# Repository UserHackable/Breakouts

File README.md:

## Breakouts

A bunch of random breakout boards
## 4ButtonBreakout 

### Board dimensions

* (165000, 125000) original units
* (1.6500, 1.2500) inches
* (41.9100, 31.7500) mm

[gerbers](4ButtonBreakout_gerber.zip?raw=true)

| Front | Back |
| --- | --- |
|  |  |

## 5MMHexaStellaBreakout 

### Board dimensions

* (100000, 100000) original units
* (1.0000, 1.0000) inches
* (25.4000, 25.4000) mm

[gerbers](5MMHexaStellaBreakout_gerber.zip?raw=true)

| Front | Back |
| --- | --- |
|  |  |

## Joystick 

### Board dimensions

* (110000, 125000) original units
* (1.1000, 1.2500) inches
* (27.9400, 31.7500) mm

[gerbers](Joystick_gerber.zip?raw=true)

| Front | Back |
| --- | --- |
|  |  |

## Led_Bar 

### Board dimensions

* (150000, 45000) original units
* (1.5000, 0.4500) inches
* (38.1000, 11.4300) mm

[gerbers](Led_Bar_gerber.zip?raw=true)

| Front | Back |
| --- | --- |
|  |  |

## MinimalDigitalAmp 

### Board dimensions

* (100000, 69994) original units
* (1.0000, 0.6999) inches
* (25.4000, 17.7785) mm

[gerbers](MinimalDigitalAmp_gerber.zip?raw=true)

| Front | Back |
| --- | --- |
|  |  |

## SingleToggleBreakout 

### Board dimensions

* (60000, 64993) original units
* (0.6000, 0.6499) inches
* (15.2400, 16.5082) mm

[gerbers](SingleToggleBreakout_gerber.zip?raw=true)

| Front | Back |
| --- | --- |
|  |  |

## UsbA 

### Board dimensions

* (99951, 47461) original units
* (0.9995, 0.4746) inches
* (25.3876, 12.0551) mm

[gerbers](UsbA_gerber.zip?raw=true)

| Front | Back |
| --- | --- |
|  |  |

## USBMiniBPower 

### Board dimensions

* (70000, 50000) original units
* (0.7000, 0.5000) inches
* (17.7800, 12.7000) mm

[gerbers](USBMiniBPower_gerber.zip?raw=true)

| Front | Back |
| --- | --- |
|  |  |

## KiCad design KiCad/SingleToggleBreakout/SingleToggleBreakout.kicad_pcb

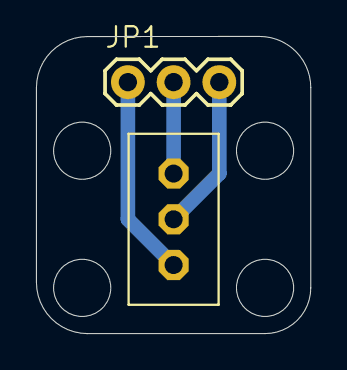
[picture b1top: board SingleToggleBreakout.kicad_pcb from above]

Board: 2 copper layers, 15.2 x 16.5 mm, 6 parts (0 on the bottom side), 3 nets.

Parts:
JP1: 1X03
U$1: SPDTSPDT; TOGGLE_SPDT
UNK_HOLE_0: dummyfp0
UNK_HOLE_1: dummyfp1
UNK_HOLE_2: dummyfp2
UNK_HOLE_3: dummyfp3

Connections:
5V: JP1.2, U$1.3
GND: JP1.1, U$1.1
unnamed: JP1.3, U$1.2

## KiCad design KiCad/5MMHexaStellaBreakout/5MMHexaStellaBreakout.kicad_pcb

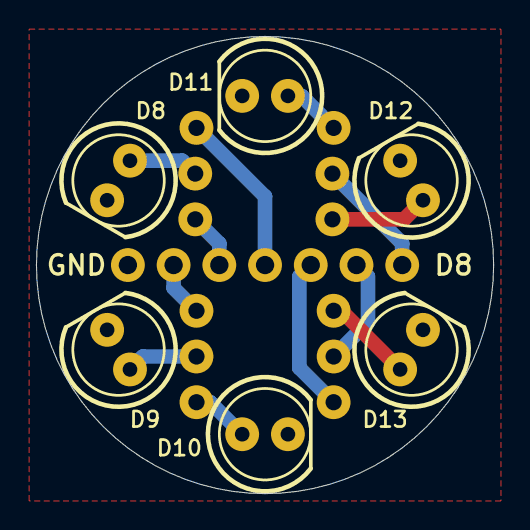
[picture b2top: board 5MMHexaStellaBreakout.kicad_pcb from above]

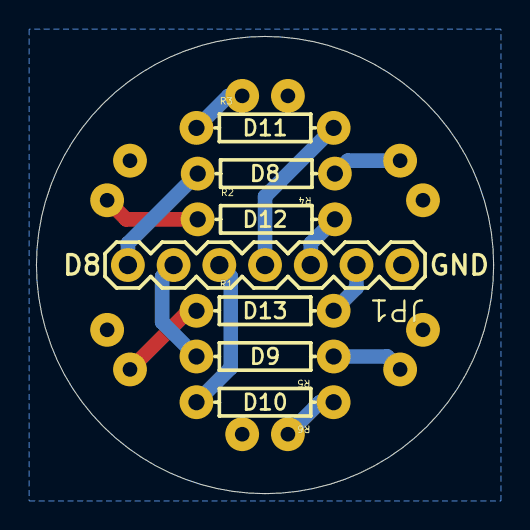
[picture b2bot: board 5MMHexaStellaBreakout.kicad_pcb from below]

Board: 2 copper layers, 25.4 x 25.4 mm, 13 parts (7 on the bottom side), 13 nets.

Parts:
JP1: 1X07
LED1, LED2, LED3, LED4, LED5, LED6: LED5MM
R1, R2, R3, R4, R5, R6: AXIAL-0.3

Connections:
D8: JP1.7, R4.P$2
D9: JP1.6, R5.P$2
D10: JP1.5, R6.P$2
D11: JP1.4, R3.P$2
D12: JP1.3, R2.P$2
D13: JP1.2, R1.P$2
GND: JP1.1, LED1.K, LED2.K, LED3.K, LED4.K, LED5.K, LED6.K
unnamed: LED1.A, R1.P$1
unnamed: LED4.A, R4.P$1
unnamed: LED2.A, R2.P$1
unnamed: LED5.A, R5.P$1
unnamed: LED3.A, R3.P$1
unnamed: LED6.A, R6.P$1

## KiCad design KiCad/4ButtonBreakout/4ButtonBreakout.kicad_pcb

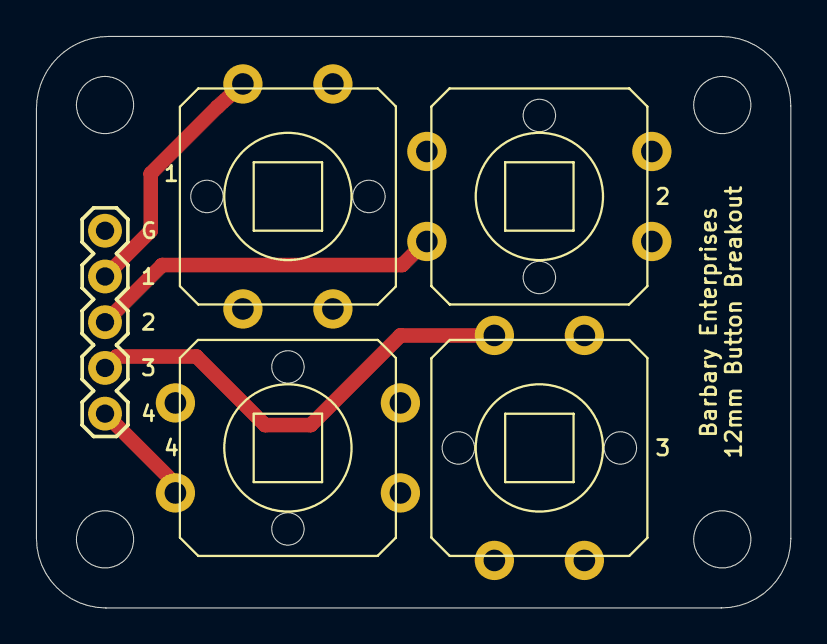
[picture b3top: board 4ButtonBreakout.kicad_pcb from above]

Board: 2 copper layers, 41.9 x 31.8 mm, 9 parts (0 on the bottom side), 5 nets.

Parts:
JP1: 1X05
S1, S2, S3, S4: B3F_10
UNK_HOLE_0: dummyfp0
UNK_HOLE_1: dummyfp1
UNK_HOLE_2: dummyfp2
UNK_HOLE_3: dummyfp3

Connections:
GND: JP1.1, S1.4, S2.4, S3.4, S4.4
unnamed: JP1.5, S1.2
unnamed: JP1.4, S2.2
unnamed: JP1.3, S3.2
unnamed: JP1.2, S4.2

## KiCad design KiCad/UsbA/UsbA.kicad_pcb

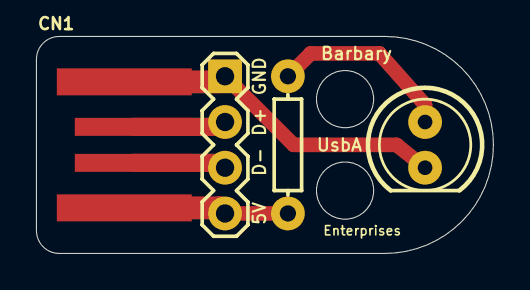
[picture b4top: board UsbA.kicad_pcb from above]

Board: 2 copper layers, 25.4 x 12.1 mm, 6 parts (0 on the bottom side), 5 nets.

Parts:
CN1: USBA_PCB
JP1: 1X04
LED1: LED5MM
R1: AXIAL-0.3
UNK_HOLE_0: dummyfp0
UNK_HOLE_1: dummyfp1

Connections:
5V: CN1.VCC, JP1.4, R1.P$2
D+: CN1.USB_PLUS, JP1.2
D-: CN1.USB_NEG, JP1.3
GND: CN1.GND, JP1.1, LED1.K
unnamed: LED1.A, R1.P$1

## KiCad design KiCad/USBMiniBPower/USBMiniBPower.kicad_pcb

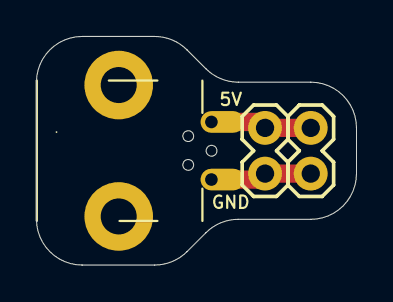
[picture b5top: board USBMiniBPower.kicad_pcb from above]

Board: 2 copper layers, 17.8 x 12.7 mm, 3 parts (0 on the bottom side), 2 nets.

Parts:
JP1, JP2: M02PTH; 1X02
U$1: USB-PWR; USB-MINIB-THM-MOLEX-PWRONLY

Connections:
5V: JP1.2, JP2.2, U$1.VBUS
GND: JP1.1, JP2.1, U$1.GND

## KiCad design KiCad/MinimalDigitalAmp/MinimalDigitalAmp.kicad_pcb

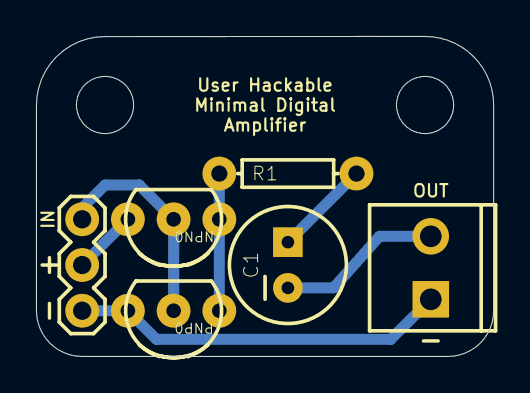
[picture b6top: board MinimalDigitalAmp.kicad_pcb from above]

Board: 2 copper layers, 25.4 x 17.8 mm, 8 parts (0 on the bottom side), 6 nets.

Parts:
C1: CPOL-RADIAL-100UF-25V
JP1: 1X03
JP2: M023.5MM; SCREWTERMINAL-3.5MM-2
NPN0: TO-92-AMMO
PNP0: TO-92-AMMO
R1: AXIAL-0.3
UNK_HOLE_0: dummyfp0
UNK_HOLE_1: dummyfp1

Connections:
GND: JP1.1, JP2.1, PNP0.3
unnamed: C1.1, R1.P$2
unnamed: C1.2, JP2.2
unnamed: JP1.3, NPN0.2, PNP0.2
unnamed: NPN0.1, PNP0.1, R1.P$1
VCC: JP1.2, NPN0.3

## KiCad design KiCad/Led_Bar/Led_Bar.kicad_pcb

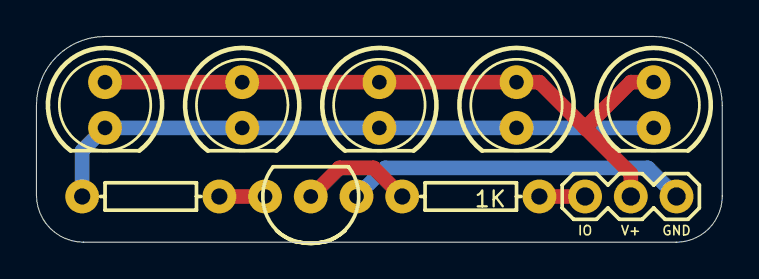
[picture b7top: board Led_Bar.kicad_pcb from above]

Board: 2 copper layers, 38.1 x 11.4 mm, 9 parts (0 on the bottom side), 6 nets.

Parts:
JP1: 1X03
LED1, LED2, LED3, LED4, LED5: LED5MM
Q1: TO-92-AMMO
R1: 1K; AXIAL-0.3
R2: AXIAL-0.3

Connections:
GND: JP1.1, Q1.1
unnamed: Q1.2, R1.P$2
unnamed: JP1.3, R1.P$1
unnamed: Q1.3, R2.P$2
unnamed: LED1.K, LED2.K, LED3.K, LED4.K, LED5.K, R2.P$1
VCC: JP1.2, LED1.A, LED2.A, LED3.A, LED4.A, LED5.A

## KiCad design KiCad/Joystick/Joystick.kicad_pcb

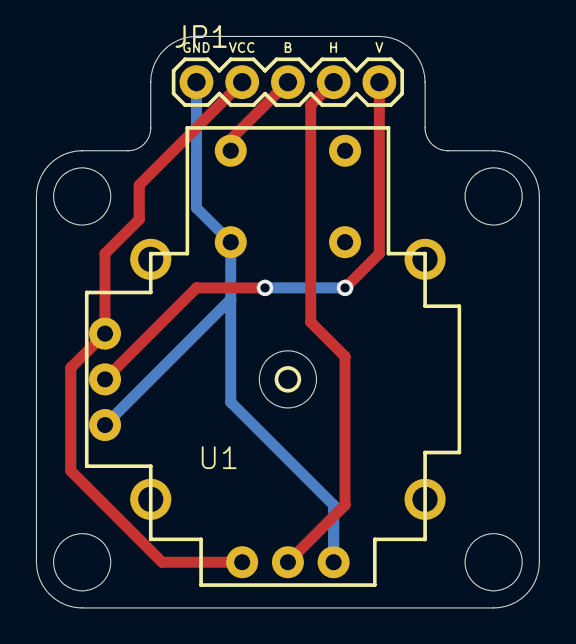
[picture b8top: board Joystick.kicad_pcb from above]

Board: 2 copper layers, 27.9 x 31.8 mm, 7 parts (0 on the bottom side), 5 nets.

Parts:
JP1: 1X05
U1: JOYSTICKPTH; JOYSTICK
UNK_HOLE_0: dummyfp0
UNK_HOLE_1: dummyfp1
UNK_HOLE_2: dummyfp2
UNK_HOLE_3: dummyfp3
UNK_HOLE_4: dummyfp4

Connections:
B: JP1.3, U1.B1A
GND: JP1.1, U1.B2A, U1.H3, U1.V3
H: JP1.4, U1.H2
V: JP1.5, U1.V2
VCC: JP1.2, U1.H1, U1.V1

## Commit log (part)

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2016-04-08 from Makefile
2016-04-08 cleaning out temps
